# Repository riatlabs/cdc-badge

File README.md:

# CDC Badge

Electronic hacker badge for the [Critical Decentralization Cluster](https://decentral.community),
featuring the [TROPIC01](https://github.com/tropicsquare/tropic01) secure
element with an [ESP32-S3](https://www.espressif.com/en/products/socs/esp32-s3/) microcontroller.

Meant to be used for workshops and prototyping. It can also be worn as a mobile
badge. Features an e-paper display with frontlight, a JST connector for
single-cell LiPo batteries and a 12-button keypad.

Repository contents:
- [cdc-badge](/cdc-badge) - KiCAD project with schematics and PCB
  layout.
- [cases](/cases) - 3D printable cases.
- [docs](/docs) - Detailed documentation including datasheets and design
  decisions.
- [utils](/utils) - Miscellaneous scripts.

## Firmware
- [cdc-badge-os](https://github.com/krim404/cdc-badge-os) - Fully featured,
  modular and extensible firmware built with PlatformIO and ESP-IDF. Uses the
  TROPIC01 to build an hardware-backed key vault with support for FIDO2,
  TOTP, SSH/GPG keys and regular passwords. Also does badge functionally:
  nametag and vCard sharing.
- [xmr-cdc-badge](https://codeberg.org/telliandev/xmr-cdc-badge) - A Monero
  hardware wallet running on the CDC Badge. Built with PlatformIO.
- [cdc-badge-esphome](https://github.com/gretel/cdc-badge-esphome) - Port of
  [ESPHome](https://esphome.io). Turns the badge into a smart home device
  connected to [Home Assistant](https://www.home-assistant.io).
- [rugart](https://gitlab.com/roosemberth/rugart) - Standards-compliant PIV
  smartcard over USB CCID developed in Rust.
- [cdc-badge-nametag](https://github.com/riatlabs/cdc-badge-nametag) - Simple
  nametag with frontlight control. Built with PlatformIO.

In order to safely operate the hardware, firmware developers should take into
account all the points in the [firmware checklist](/docs/firmware-checklist.md).

The [cdc-badge-qc-firmware](https://github.com/riatlabs/cdc-badge-qc-firmware)
repo contains test batteries which make sure the hardware is working as
expected.

### Flashing
Options:
1. Via USB.
2. Via UART. TX and RX are broken out to the Raspberry Pi header on pins 8 and 10.
   The reset and flash buttons are physically placed near the ESP32.

When flashing a badge for the first time over USB you may need to press the
classic flash + reset button sequence in order to get it out of a boot loop.

## Example applications
- Interactive name tag
- Social networking games
- Monero hardware wallet
- Reticulum node with secure key storage and ECC acceleration
- FIDO2 keystore
- Pager and short message chatting
- Local AI with the Sipeed M1 HAT: e.g. voice activated control

## Expansions
The badge has 3 expansion ports:
- Raspberry Pi [40 pin GPIO header](https://pinout.xyz) ready to take any [HAT or pHAT](https://pinout.xyz/boards)
- [SAO](https://badge.team/docs/standards/sao/) ~~Shitty~~ Standardized Add-On
  port to connect small PCBs with blinky LEDs, speakers, and other bling.
- [Grove](https://wiki.seeedstudio.com/Grove_System) compatible connector to
  interface with any Grove sensor or network module. Has selectable output
  voltage (3.3 V or 5 V).

The [Grove AI HAT for Edge Computing](https://wiki.seeedstudio.com/Grove_AI_HAT_for_Edge_Computing/)
is a good pairing for more demanding applications. It is based on the [Kendryte
K210 SoC](https://www.kendryte.com/en/proDetail/210) which has 2 RISC-V 64 bit
cores and many custom accelerators (AI/NPU/CNN, audio, FFT, AES, SHA256).

### SPI to internal devices
It is possible to interface via SPI from the Raspberry Pi header to the e-paper
display and the TROPIC01. There are 2 mechanical sliding switches which you can
use to connect pin 24 and pin 26 to the chip select (CS) of these devices.

The auxiliary signals from the e-paper display (DC, RST, BUSY) are available on
pins 29, 31 and 36. The interrupt signal from TROPIC01 is available on pin 37.

This allows an external microcontroller, for instance the Sipeed M1, to display
graphics on the screen and use the secure element.

### Buttons
Besides the reset and flash buttons (directly connected to the ESP32) there are
12 buttons connected to the TCA9535 IO Expader. These can be access through I²C
and used as keypad for user input.

These is also a button (PW ON / RESET) directly connected to the BQ25895
charging IC. It has fixed functionality:
- If the BQ25895 is set to shipping mode (output power disabled), pressing the
  PW ON / RESET button for 2s disables the shipping mode and allows power to flow to the
  ESP32.
- During battery-powered operation (i.e. no charger is plugged in), pressing the
  PW ON / RESET for 12s forces a full power reset.

## Power characteristics

### Maximum
The maximum total current that can be drawn out of the power bus is:
- 3.3 V: 2 A
- 5 V: 2.5 A

Take into account that all badge components (ESP32, TROPIC01, display, etc.)
draw their power from the 3.3 V bus.

### Minimum
All onboard ICs have very low quiescent currents, under 40 μA. Even the ESP32-S3
can go as low as 8 μA in it's deep sleep mode (240 μA in light sleep mode). The
major exception is the TROPIC01 which draws 945 μA in sleep mode.

If a use case requires the lowest power usage possible, the exposed copper trace
connecting VCC to the TROPIC01 should be cut. It can later be reconnected with a
0 Ω resistor or a wire (0603 pads available). This exposed trace can also be
used to do power glitch testing on the TROPIC01.

On most use cases the sleep mode power usage of the TROPIC01 will be
insignificant though. For instance, while listening for WiFi transmissions, the
ESP32-S3 draws 95 mA. The TROPIC01 sleep mode current is just 1% of this.

## Manufacturing
There's a [Makefile](/cdc-badge/Makefile) to generate the fabrication
outputs.

To run it you need the following dependencies installed in your system:
- A Make implementation, e.g. [GNU Make](https://www.gnu.org/software/make/),
  packaged in most distros as `make`.
- [KiKit](https://yaqwsx.github.io/KiKit/latest/installation/intro/),
  packaged [in Arch as python-kikit](https://archlinux.org/packages/extra/any/python-kikit/)
  and [in NixOs as kikit](https://search.nixos.org/packages?show=kikit).

Running `make` in the `cdc-badge` directory will output the fabrication files
into the `production/` directory.

So far outputs are created just for JLCPCB, but [other manufacturers can be
easily supported](https://yaqwsx.github.io/KiKit/latest/fabrication/intro/#currently-supported).

### Panelization
Panelization is an intermediate step in the fabrication outputs generation
detailed above, but it can be run independently. `make panel` generates a 1x2
panel of the PCB into `production/panel.kicad_pcb`. This panel is the preferred
way to send the badge for fabrication. It reduces costs while preserving a rigid
structure.

## Further documentation
Please check:
- the [docs](/docs/) directory;
- the [KiCad schematics](/cdc-badge/cdc-badge.kicad_sch) (available as PDF in
  the [releases](https://github.com/riatlabs/cdc-badge/releases));

## Acknowledgments
We would like to thank:

* **ceetee**, for all the in-depth reviews, and for making us aware that we are
guiding electromagnetic waves through the dielectric and not moving water
through pipes.

* **krim**, for the tireless firmware development.

## License and authorship
Copyright © 2025-2026 RIAT Institute

Licensed under [CERN Open Hardware Licence Version 2 - Permissive](/LICENSE).

Third-party resources' authorship and license information in [AUTHORS.md](/AUTHORS.md)

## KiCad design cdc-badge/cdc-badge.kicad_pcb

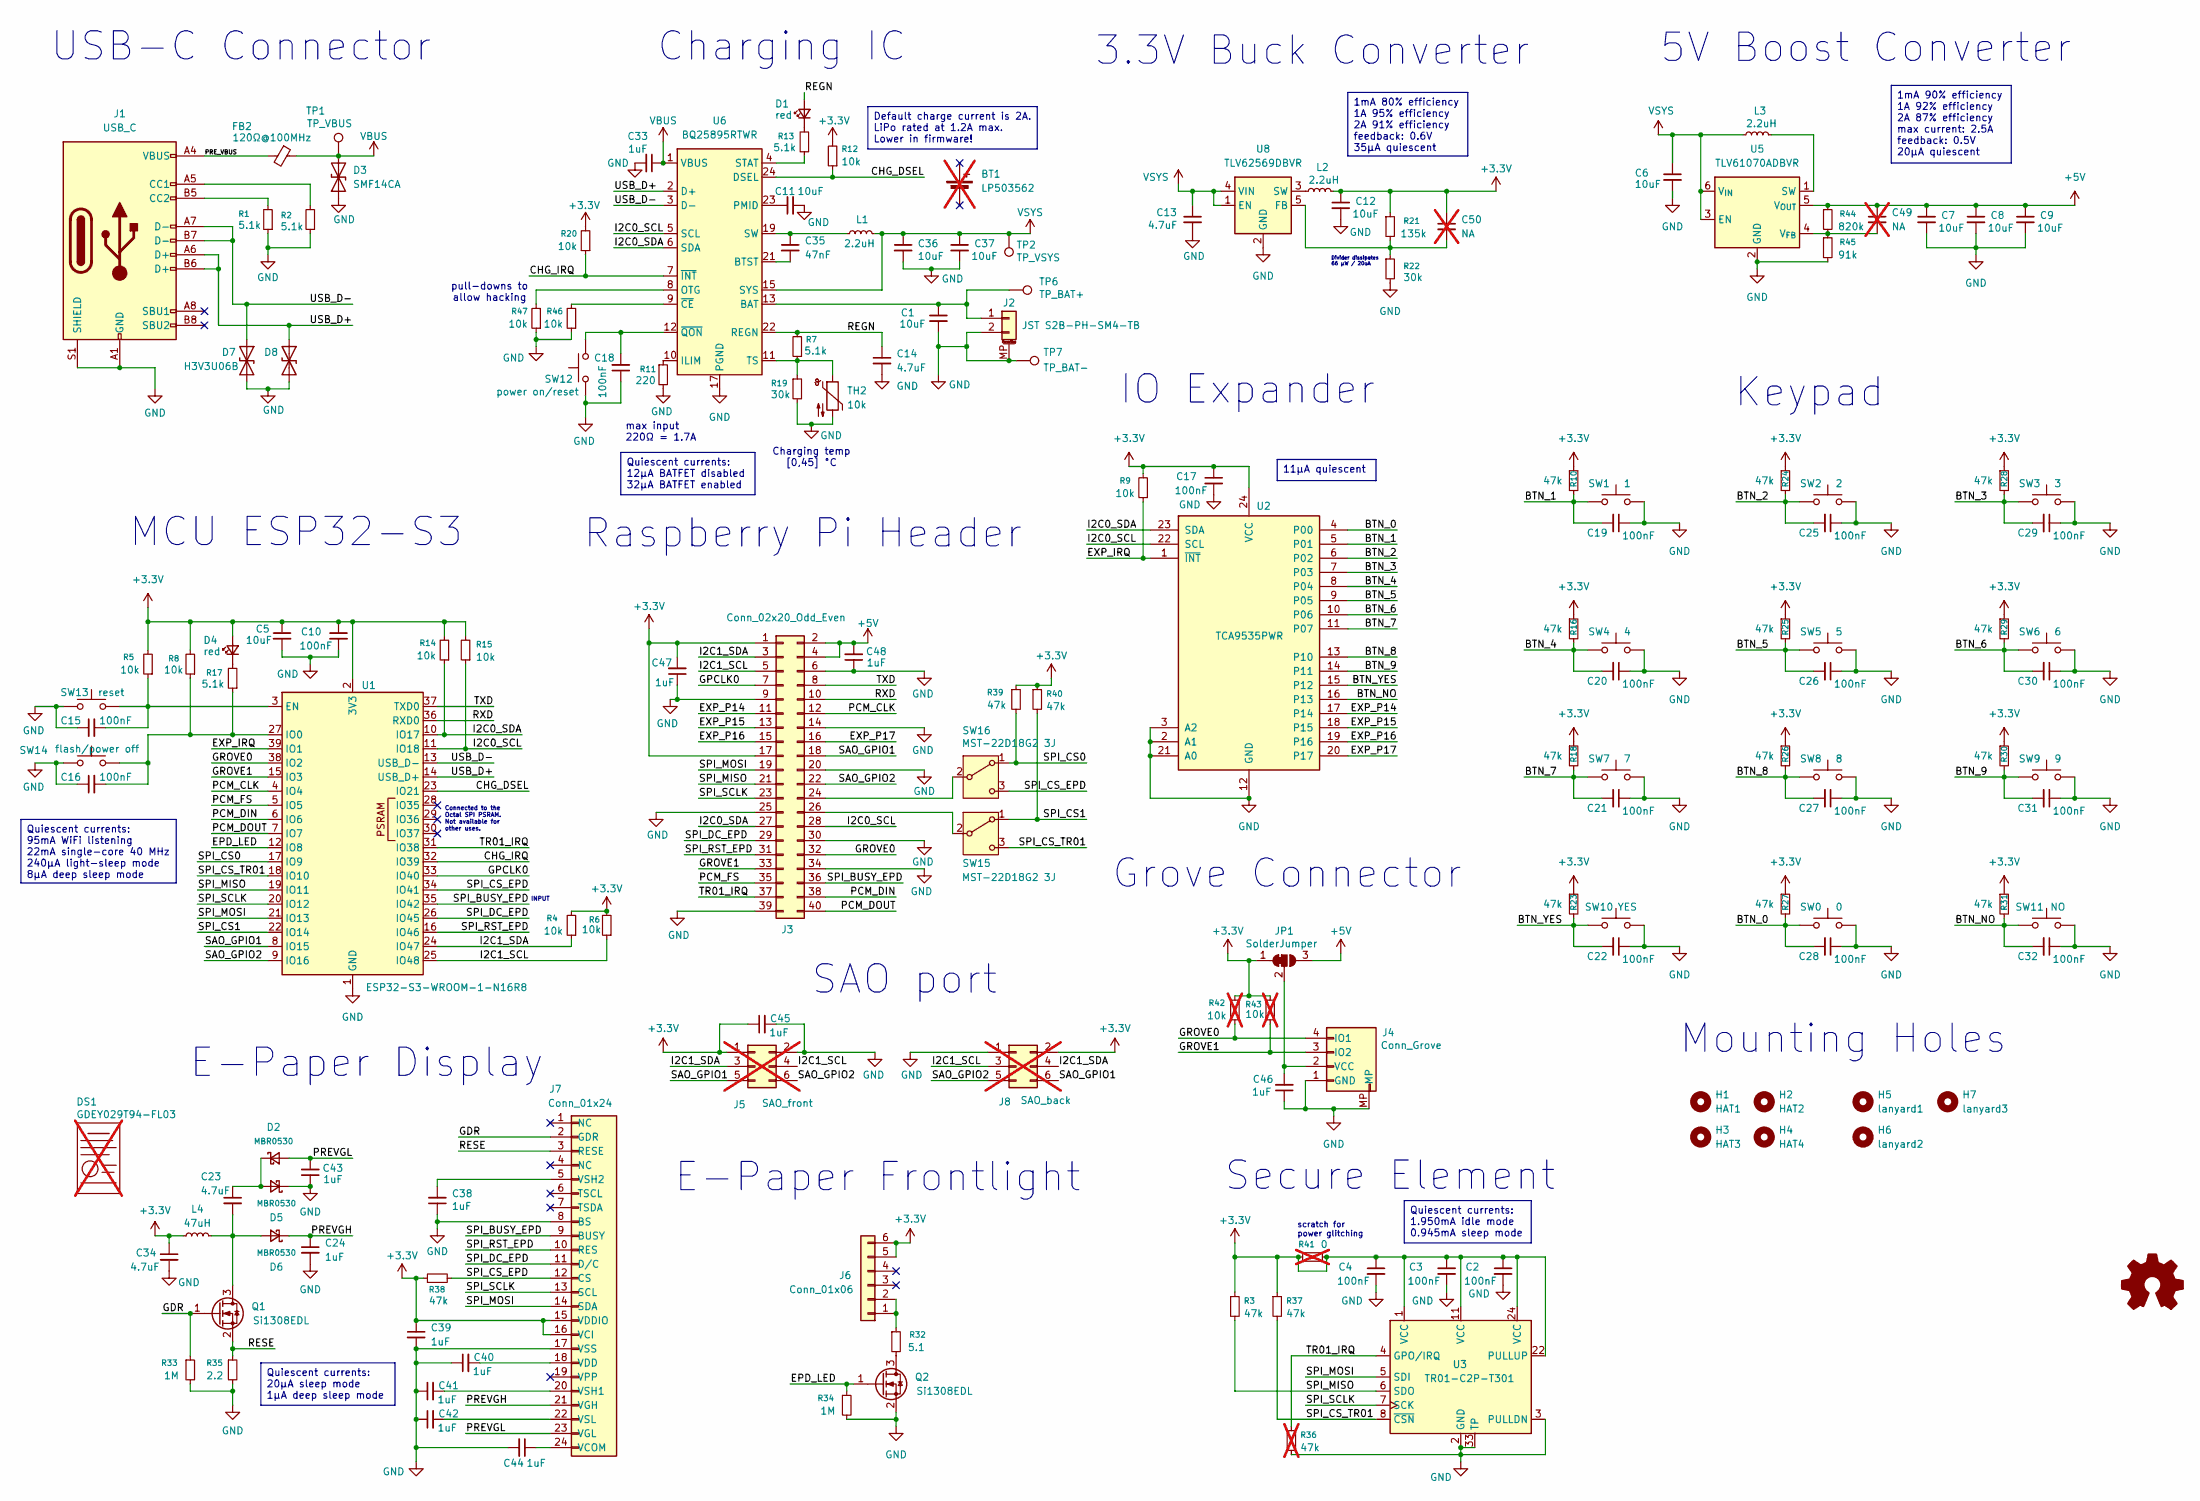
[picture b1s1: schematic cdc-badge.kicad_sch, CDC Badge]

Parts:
BT1: LP503562; PKCELL_LP503562_invert; not fitted
C1, C5, C6, C7, C8, C9, C11, C12, C36, C37: 10uF; C_0805_2012Metric; MPN CL21A106KAYNNNE; JLCPCB PN C15850
C2, C3, C4, C10, C15, C16, C17, C18, C19, C20, C21, C22, C25, C26, C27, C28, C29, C30, C31, C32: 100nF; C_0603_1608Metric; MPN CC0603KRX7R9BB104; JLCPCB PN C14663
C13, C14, C23, C34: 4.7uF; C_0805_2012Metric; MPN CL21A475KAQNNNE; JLCPCB PN C1779
C24, C33, C38, C39, C40, C41, C42, C43, C44, C45, C46, C47, C48: 1uF; C_0603_1608Metric; MPN CL10A105KB8NNNC; JLCPCB PN C15849
C35: 47nF; C_0603_1608Metric; MPN CL10B473KB8NNNC; JLCPCB PN C1622
C49, C50: NA; C_0603_1608Metric; not fitted
D1, D4: red; LED_0603_1608Metric; MPN KT-0603R; JLCPCB PN C2286
D2, D5, D6: MBR0530; D_SOD-123; MPN MBR0530T1G; JLCPCB PN C82046
D3: SMF14CA; D_SOD-123FL_Unpolarized; MPN SMF14CA; JLCPCB PN C41411783
D7, D8: H3V3U06B; D_DFN0603-2L_Unpolarized; MPN H3V3U06B; JLCPCB PN C20617908
DS1: GDEY029T94-FL03; not fitted
FB2: 120Ω@100MHz; L_0805_2012Metric; MPN HCB2012KF-121T50; JLCPCB PN C304323
H1: HAT1; MountingHole_2.7mm_KeepOut
H2: HAT2; MountingHole_2.7mm_KeepOut
H3: HAT3; MountingHole_2.7mm_KeepOut
H4: HAT4; MountingHole_2.7mm_KeepOut
H5: lanyard1; MountingHole_5.5mm
H6: lanyard2; MountingHole_5.5mm
H7: lanyard3; MountingHole_5.5mm
J1: USB_C; SHOUHAN_TYPE-C_16PIN_2MD_073; MPN TYPE-C 16PIN 2MD(073); JLCPCB PN C2765186
J2: JST S2B-PH-SM4-TB; JST_PH_S2B-PH-SM4-TB_1x02-1MP_P2.00mm_Horizontal; JLCPCB PN C295747
J3: Conn_02x20_Odd_Even; PinHeader_2x20_P2.54mm_Vertical_SMD; MPN HB-PH9-254220PB2GOW; JLCPCB PN C42396895
J4: Conn_Grove; BOOMELE_HY-4P_1x04-1MP_P2mm_Horizontal; MPN HC-HY-4AWT; JLCPCB PN C146060
J5: SAO_front; Wuerth_WR-PHD_610006243021_SMD_2x03_P2.54mm_Vertical; MPN 610006243021; not fitted
J6: Conn_01x06; Jushuo_AFC07-S06FCA-00_1x6-1MP_P0.50_Horizontal; MPN AFC07-S06FCA-00; JLCPCB PN C262553
J7: Conn_01x24; Jushuo_AFC07-S24ECA-00_1x24-1MP_P0.50_Horizontal; MPN AFC07-S24ECA-00; JLCPCB PN C262643
J8: SAO_back; Wuerth_WR-PHD_610006243021_SMD_2x03_P2.54mm_Vertical; MPN 610006243021; not fitted
JP1: SolderJumper; SolderJumper-3_P1.3mm_Bridged12_RoundedPad1.0x1.5mm
L1, L2, L3: 2.2uH; L_TechFuse_SL0420; MPN SL0420-2R2M; JLCPCB PN C22463806
L4: 47uH; L_Changjiang_FNR4030S; MPN FNR4030S470MT; JLCPCB PN C167888
Q1, Q2: Si1308EDL; SOT-323_SC-70; MPN SI1308EDL; JLCPCB PN C7603347
R1, R2, R7, R13, R17: 5.1k; R_0603_1608Metric; MPN 0603WAF5101T5E; JLCPCB PN C23186
R3, R10, R16, R18, R23, R24, R25, R26, R27, R28, R29, R30, R31, R37, R38, R39, R40: 47k; R_0603_1608Metric; MPN 0603WAF4702T5E; JLCPCB PN C25819
R4, R5, R6, R8, R9, R12, R14, R15, R20, R46, R47: 10k; R_0603_1608Metric; MPN 0603WAF1002T5E; JLCPCB PN C25804
R11: 220; R_0603_1608Metric; MPN 0603WAF2200T5E; JLCPCB PN C22962
R19, R22: 30k; R_0603_1608Metric; MPN 0603WAF3002T5E; JLCPCB PN C22984
R21: 135k; R_0603_1608Metric; MPN RT0603BRD07135KL; JLCPCB PN C861113
R32: 5.1; R_0603_1608Metric; MPN 0603WAF510KT5E; JLCPCB PN C25197
R33, R34: 1M; R_0603_1608Metric; MPN 0603WAF1004T5E; JLCPCB PN C22935
R35: 2.2; R_0603_1608Metric; MPN 0603WAF220KT5E; JLCPCB PN C22939
R36: 47k; R_0603_1608Metric; MPN 0603WAF4702T5E; JLCPCB PN C25819; not fitted
R41: 0; R_0603_1608Metric; MPN 0603WAF0000T5E; JLCPCB PN C21189; not fitted
R42, R43: 10k; R_0603_1608Metric; MPN 0603WAF1002T5E; JLCPCB PN C25804; not fitted
R44: 820k; R_0603_1608Metric; MPN RC0603FR-07820KL; JLCPCB PN C141684
R45: 91k; R_0603_1608Metric; MPN 0603WAF9102T5E; JLCPCB PN C23265
SW0: 0; SW_Push_1P1T_NO_TS1145x; MPN TS114516025; JLCPCB PN C22375312
SW1: 1; SW_Push_1P1T_NO_TS1145x; MPN TS114516025; JLCPCB PN C22375312
SW2: 2; SW_Push_1P1T_NO_TS1145x; MPN TS114516025; JLCPCB PN C22375312
SW3: 3; SW_Push_1P1T_NO_TS1145x; MPN TS114516025; JLCPCB PN C22375312
SW4: 4; SW_Push_1P1T_NO_TS1145x; MPN TS114516025; JLCPCB PN C22375312
SW5: 5; SW_Push_1P1T_NO_TS1145x; MPN TS114516025; JLCPCB PN C22375312
SW6: 6; SW_Push_1P1T_NO_TS1145x; MPN TS114516025; JLCPCB PN C22375312
SW7: 7; SW_Push_1P1T_NO_TS1145x; MPN TS114516025; JLCPCB PN C22375312
SW8: 8; SW_Push_1P1T_NO_TS1145x; MPN TS114516025; JLCPCB PN C22375312
SW9: 9; SW_Push_1P1T_NO_TS1145x; MPN TS114516025; JLCPCB PN C22375312
SW10: YES; SW_Push_1P1T_NO_TS1145x; MPN TS114516025; JLCPCB PN C22375312
SW11: NO; SW_Push_1P1T_NO_TS1145x; MPN TS114516025; JLCPCB PN C22375312
SW12: power on/reset; SW_Push_1P1T_NO_TS1145x; MPN TS114516025; JLCPCB PN C22375312
SW13: reset; SW_Push_1P1T_NO_TS1145x; MPN TS114516025; JLCPCB PN C22375312
SW14: flash/power off; SW_Push_1P1T_NO_TS1145x; MPN TS114516025; JLCPCB PN C22375312
SW15, SW16: MST-22D18G2 3J; SW_SPDT_Shouhan_MST-22D18G2_3J; MPN MST-22D18G2 3J; JLCPCB PN C2875122
TH2: 10k; R_0603_1608Metric; MPN B57332V5103F360; JLCPCB PN C209893
TP1: TP_VBUS; TestPoint_Pad_D2.0mm
TP2: TP_VSYS; TestPoint_Pad_D2.0mm
TP6: TP_BAT+; TestPoint_Pad_D2.0mm
TP7: TP_BAT-; TestPoint_Pad_D2.0mm
U1: ESP32-S3-WROOM-1-N16R8; ESP32-S3-WROOM-1; MPN ESP32-S3-WROOM-1-N16R8; JLCPCB PN C2913202
U2: TCA9535PWR; TSSOP-24_4.4x7.8mm_P0.65mm; MPN TCA9535PWR; JLCPCB PN C130204
U3: TR01-C2P-T301; QFN-32-1EP_4x4mm_P0.4mm_EP2.9x2.9mm; JLCPCB PN C9900235223
U5: TLV61070ADBVR; SOT-23-6; MPN TLV61070ADBVR; JLCPCB PN C6881375
U6: BQ25895RTWR; Texas_RTW_WQFN-24-1EP_4x4mm_P0.5mm_EP2.7x2.7mm_0.3mmThermal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; MPN BQ25895RTWR; JLCPCB PN C80200
U8: TLV62569DBVR; SOT-23-5; MPN TLV62569DBVR; JLCPCB PN C141836

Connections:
+3.3V: C2.1, C3.1, C4.1, C5.1, C10.1, C12.1, C17.1, C34.1, C39.1, C45.1, C47.2, C50.1, D4.2 (A), J3.1, J3.17, J5.1, J6.5, J6.6, J7.15 (VDDIO), J7.16 (VCI), J8.2, JP1.1 (A), L2.2, L4.1, R3.1, R4.2, R5.2, R6.2, R8.2, R9.2, R10.1, R12.2, R14.2, R15.2, R16.1, R18.1, R20.2, R21.1, R23.1, R24.1, R25.1, R26.1, R27.1, R28.1, R29.1, R30.1, R31.1, R37.1, R38.1, R39.1, R40.1, R41.1, R41.2, R42.2, R43.2, U1.2 (3V3), U2.24 (VCC), U3.1 (VCC), U3.11 (VCC), U3.22 (PULLUP), U3.24 (VCC)
+5V: C7.1, C8.1, C9.1, C48.2, C49.1, J3.2, J3.4, JP1.3 (B), R44.1, U5.5 (V_{OUT})
/BTN_0: C28.2, R27.2, SW0.1, U2.4 (P00)
/BTN_1: C19.2, R10.2, SW1.1, U2.5 (P01)
/BTN_2: C25.2, R24.2, SW2.1, U2.6 (P02)
/BTN_3: C29.2, R28.2, SW3.1, U2.7 (P03)
/BTN_4: C20.2, R16.2, SW4.1, U2.8 (P04)
/BTN_5: C26.2, R25.2, SW5.1, U2.9 (P05)
/BTN_6: C30.2, R29.2, SW6.1, U2.10 (P06)
/BTN_7: C21.2, R18.2, SW7.1, U2.11 (P07)
/BTN_8: C27.2, R26.2, SW8.1, U2.13 (P10)
/BTN_9: C31.2, R30.2, SW9.1, U2.14 (P11)
/BTN_NO: C32.2, R31.2, SW11.1, U2.16 (P13)
/BTN_YES: C22.2, R23.2, SW10.1, U2.15 (P12)
/CHG_DSEL: R12.1, U1.23 (IO21), U6.24 (DSEL)
/CHG_IRQ: R20.1, U1.32 (IO39), U6.7 (~INT)
/EPD_LED: Q2.1 (G), R34.1, U1.12 (IO8)
/EXP_IRQ: R9.1, U1.39 (IO1), U2.1 (~INT)
/EXP_P14: J3.11, U2.17 (P14)
/EXP_P15: J3.13, U2.18 (P15)
/EXP_P16: J3.15, U2.19 (P16)
/EXP_P17: J3.16, U2.20 (P17)
/GDR: J7.2 (GDR), Q1.1 (G), R33.1
/GPCLK0: J3.7, U1.33 (IO40)
/GROVE0: J3.32, J4.4 (IO1), R42.1, U1.38 (IO2)
/GROVE1: J3.33, J4.3 (IO2), R43.1, U1.15 (IO3)
/I2C0_SCL: J3.28, R15.1, U1.11 (IO18), U2.22 (SCL), U6.5 (SCL)
/I2C0_SDA: J3.27, R14.1, U1.10 (IO17), U2.23 (SDA), U6.6 (SDA)
/I2C1_SCL: J3.5, J5.4, J8.3, R6.1, U1.25 (IO48)
/I2C1_SDA: J3.3, J5.3, J8.4, R4.1, U1.24 (IO47)
/PCM_CLK: J3.12, U1.4 (IO4)
/PCM_DIN: J3.38, U1.6 (IO6)
/PCM_DOUT: J3.40, U1.7 (IO7)
/PCM_FS: J3.35, U1.5 (IO5)
/PREVGH: C24.1, D6.1 (K), J7.21 (VGH)
/PREVGL: C43.2, D2.2 (A), J7.23 (VGL)
/PRE_VBUS: FB2.2, J1.A4 (VBUS), J1.A9 (VBUS), J1.B4 (VBUS), J1.B9 (VBUS)
/REGN: C14.1, D1.2 (A), R7.2, U6.22 (REGN)
/RESE: J7.3 (RESE), Q1.2 (S), R35.1
/RXD: J3.10, U1.36 (RXD0)
/SAO_GPIO1: J3.18, J5.5, J8.6, U1.8 (IO15)
/SAO_GPIO2: J3.22, J5.6, J8.5, U1.9 (IO16)
/SPI_BUSY_EPD: J3.36, J7.9 (BUSY), U1.35 (IO42)
/SPI_CS0: R39.2, SW16.1 (A), U1.17 (IO9)
/SPI_CS1: R40.2, SW15.1 (A), U1.22 (IO14)
/SPI_CS_EPD: J7.12 (CS), R38.2, SW16.3 (C), U1.34 (IO41)
/SPI_CS_TR01: R37.2, SW15.3 (C), U1.18 (IO10), U3.8 (~CSN)
/SPI_DC_EPD: J3.29, J7.11 (D/C), U1.26 (IO45)
/SPI_MISO: J3.21, R3.2, U1.19 (IO11), U3.6 (SDO)
/SPI_MOSI: J3.19, J7.14 (SDA), U1.21 (IO13), U3.5 (SDI)
/SPI_RST_EPD: J3.31, J7.10 (RES), U1.16 (IO46)
/SPI_SCLK: J3.23, J7.13 (SCL), U1.20 (IO12), U3.7 (SCK)
/TR01_IRQ: J3.37, R36.1, U1.31 (IO38), U3.4 (GPO/IRQ)
/TXD: J3.8, U1.37 (TXD0)
/USB_D+: D8.1 (A1), J1.A6 (D+), J1.B6 (D+), U1.14 (USB_D+), U6.2 (D+)
/USB_D-: D7.1 (A1), J1.A7 (D-), J1.B7 (D-), U1.13 (USB_D-), U6.3 (D-)
GND: C1.2, C2.2, C3.2, C4.2, C5.2, C6.2, C7.2, C8.2, C9.2, C10.2, C11.2, C12.2, C13.2, C14.2, C15.1, C16.1, C17.2, C18.1, C19.1, C20.1, C21.1, C22.1, C24.2, C25.1, C26.1, C27.1, C28.1, C29.1, C30.1, C31.1, C32.1, C33.2, C34.2, C36.2, C37.2, C38.1, C39.2, C40.1, C41.1, C42.1, C43.1, C44.2, C45.2, C46.1, C47.1, C48.1, D3.1 (A1), D5.1 (K), D7.2 (A2), D8.2 (A2), J1.A1 (GND), J1.A12 (GND), J1.B1 (GND), J1.B12 (GND), J1.S1 (SHIELD), J2.2, J2.MP (MountPin), J3.6, J3.9, J3.14, J3.20, J3.25, J3.30, J3.34, J3.39, J4.1 (GND), J4.MP, J5.2, J7.8 (BS), J7.17 (VSS), J8.1, Q2.2 (S), R1.1, R2.1, R11.2, R19.2, R22.2, R33.2, R34.2, R35.2, R36.2, R45.2, R46.1, R47.1, SW0.2, SW1.2, SW2.2, SW3.2, SW4.2, SW5.2, SW6.2, SW7.2, SW8.2, SW9.2, SW10.2, SW11.2, SW12.1, SW13.1, SW14.1, TH2.2, TP7.1, U1.1 (GND), U1.40 (GND), U1.41 (GND), U2.2 (A1), U2.3 (A2), U2.12 (GND), U2.21 (A0), U3.2 (GND), U3.3 (PULLDN), U3.9 (PULLDN), U3.10 (PULLDN), U3.12 (GND), U3.23 (GND), U3.30 (PULLDN), U3.31 (PULLDN), U3.33 (TP), U5.2 (GND), U6.17 (PGND), U6.18 (PGND), U6.25 (PGND), U8.2 (GND)
unnamed: C35.1, L1.1, U6.19 (SW), U6.20 (SW)
unnamed: D1.1 (K), R13.2
unnamed: C23.1, D2.1 (K), D5.2 (A)
unnamed: D4.1 (K), R17.2
unnamed: C23.2, D6.2 (A), L4.2, Q1.3 (D)
unnamed: J1.A5 (CC1), R2.2
unnamed: J1.B5 (CC2), R1.2
unnamed: C1.1, J2.1, TP6.1, U6.13 (BAT), U6.14 (BAT)
unnamed: J3.24, SW16.2 (B)
unnamed: J3.26, SW15.2 (B)
unnamed: C46.2, J4.2 (VCC), JP1.2 (C)
unnamed: J6.1, J6.2, R32.1
unnamed: C44.1, J7.24 (VCOM)
unnamed: C40.2, J7.18 (VDD)
unnamed: C41.2, J7.20 (VSH1)
unnamed: C38.2, J7.5 (VSH2)
unnamed: C42.2, J7.22 (VSL)
unnamed: Q2.3 (D), R32.2
unnamed: C15.2, R5.1, SW13.2, U1.3 (EN)
unnamed: C16.2, R8.1, R17.1, SW14.2, U1.27 (IO0)
unnamed: L3.2, U5.1 (SW)
unnamed: C49.2, R44.2, R45.1, U5.4 (V_{FB})
unnamed: C35.2, U6.21 (BTST)
unnamed: R11.1, U6.10 (ILIM)
unnamed: R47.2, U6.8 (OTG)
unnamed: C11.1, U6.23 (PMID)
unnamed: R13.1, U6.4 (STAT)
unnamed: R7.1, R19.1, TH2.1, U6.11 (TS)
unnamed: R46.2, U6.9 (~CE)
unnamed: C18.2, SW12.2, U6.12 (~QON)
unnamed: C50.2, R21.2, R22.1, U8.5 (FB)
unnamed: L2.1, U8.3 (SW)
VBUS: C33.1, D3.2 (A2), FB2.1, TP1.1, U6.1 (VBUS)
VSYS: C6.1, C13.1, C36.1, C37.1, L1.2, L3.1, TP2.1, U5.3 (EN), U5.6 (V_{IN}), U6.15 (SYS), U6.16 (SYS), U8.1 (EN), U8.4 (VIN)

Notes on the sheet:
MCU ESP32-S3
Connected to the Octal SPI PSRAM. Not available for other uses.
Mounting Holes
3.3V Buck Converter
pull-downs to allow hacking
scratch for power glitching
INPUT
Charging temp [0,45] °C
USB-C Connector
E-Paper Display
Keypad
IO Expander
Grove Connector
Secure Element
Raspberry Pi Header
Divider dissipates 66 µW / 20uA
max input 220Ω = 1.7A
5V Boost Converter
SAO port
Charging IC
E-Paper Frontlight
Quiescent currents: 1.950mA idle mode 0.945mA sleep mode
Quiescent currents: 95mA WiFi listening 22mA single-core 40 MHz 240μA light-sleep mode 8μA deep sleep mode
1mA 90% efficiency 1A 92% efficiency 2A 87% efficiency max current: 2.5A feedback: 0.5V 20μA quiescent
1mA 80% efficiency 1A 95% efficiency 2A 91% efficiency feedback: 0.6V 35μA quiescent
Default charge current is 2A. LiPo rated at 1.2A max. Lower in firmware!
11μA quiescent
Quiescent currents: 12μA BATFET disabled 32μA BATFET enabled
Quiescent currents: 20μA sleep mode 1μA deep sleep mode

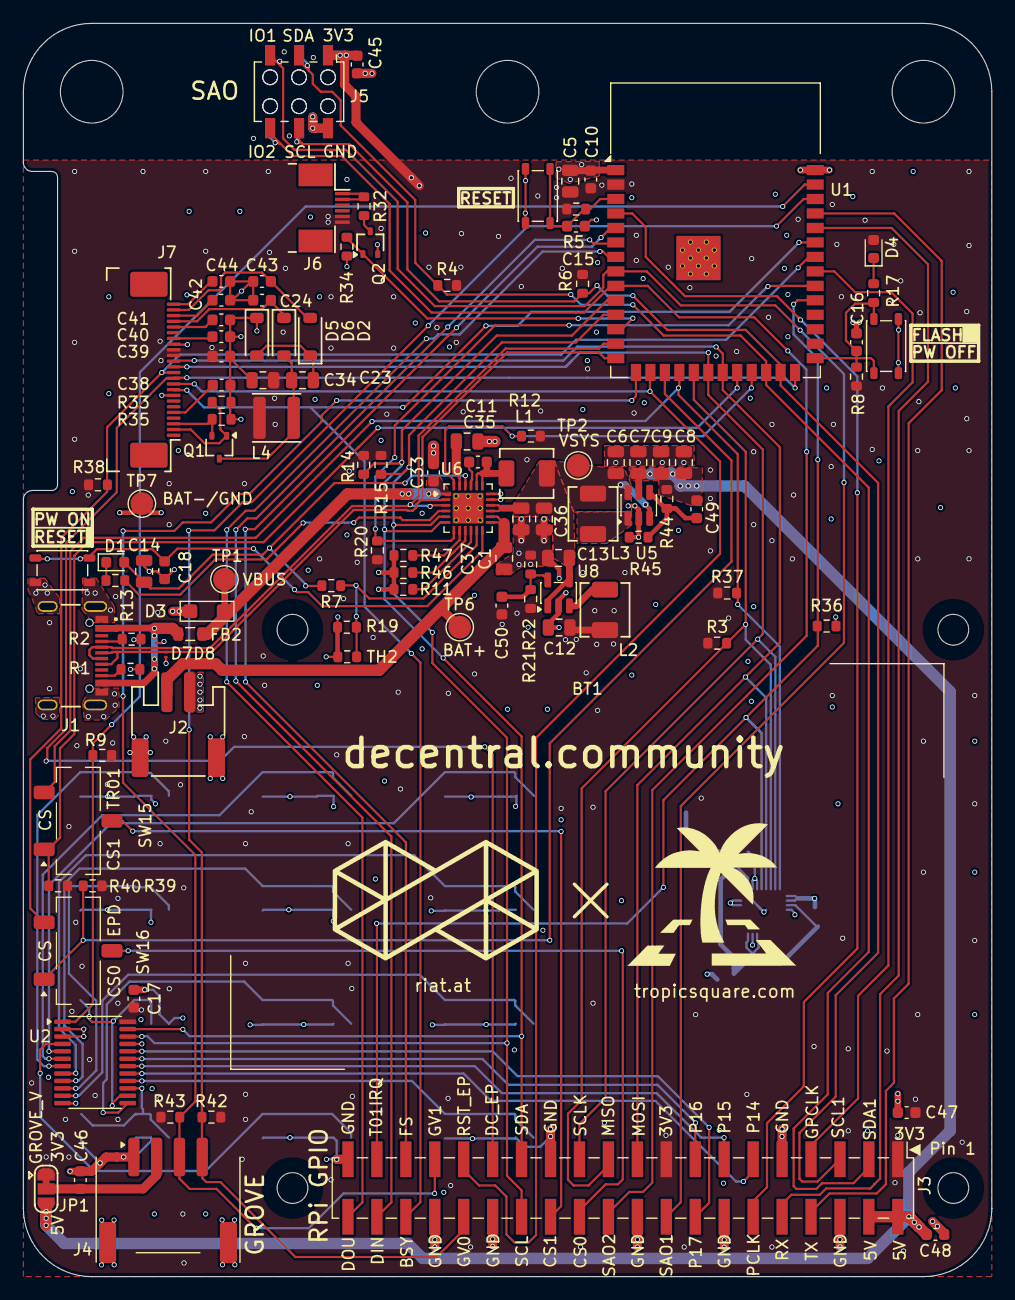
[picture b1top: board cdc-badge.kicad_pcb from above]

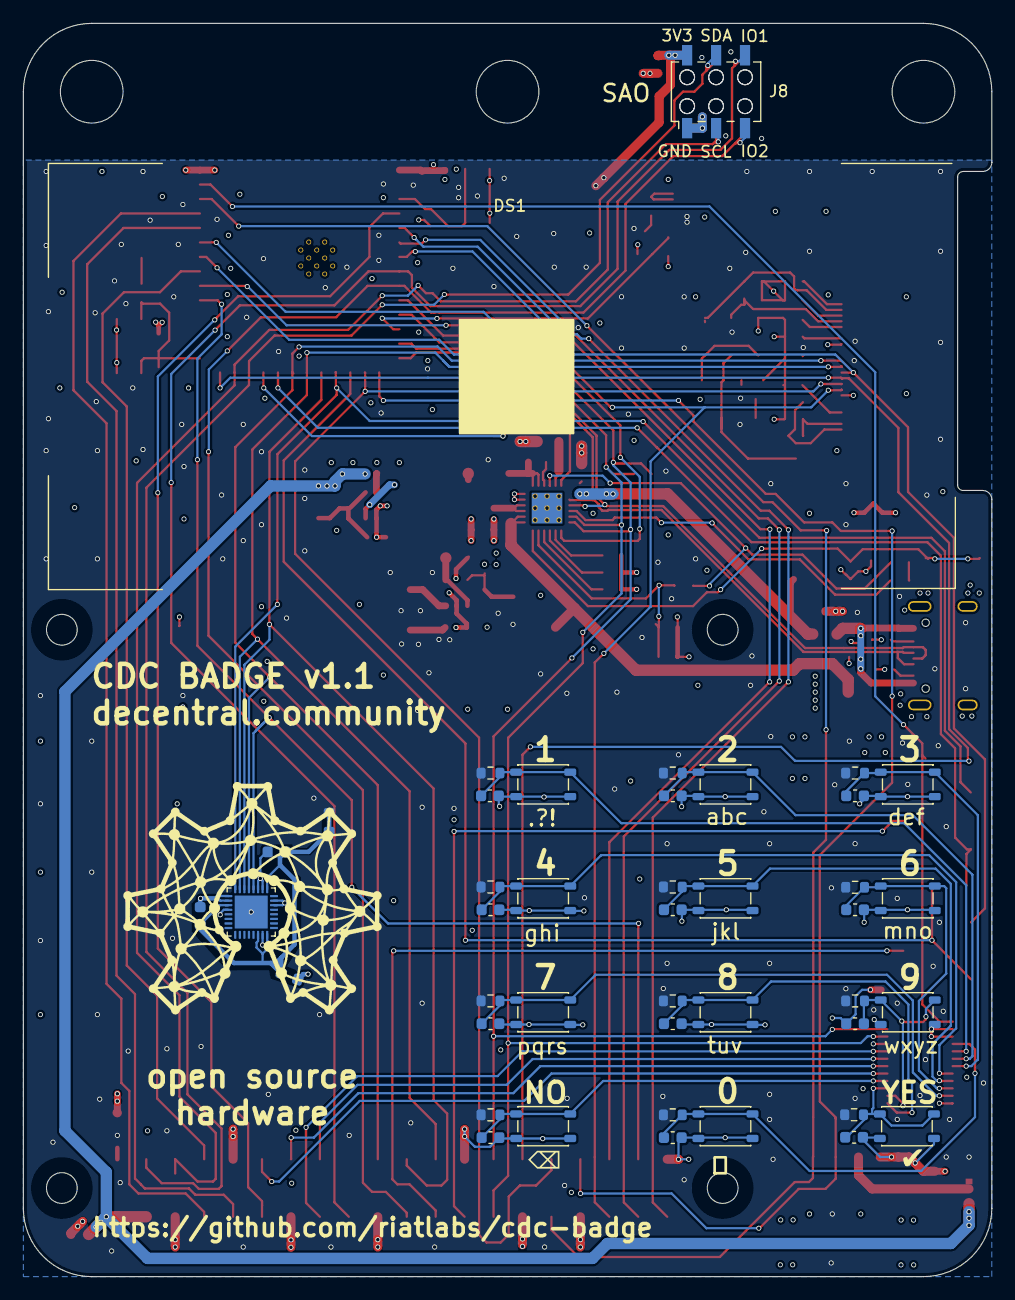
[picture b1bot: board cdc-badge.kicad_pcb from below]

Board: 4 copper layers, 85.0 x 110.0 mm, 158 parts (43 on the bottom side), 91 nets.

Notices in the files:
cdc-badge/cdc-badge.kicad_pcb:
This source describes Open Hardware and is licensed under the CERN-OHL-P v2
hardware/kicad/Sipeed-M1-v1/Sipeed-M1-v1.kicad_pcb:
Copyright © 2025 RIAT Institute
